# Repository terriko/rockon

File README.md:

# RockOn

Design notes, files and art for a decibel meter soldering kit.

[pyCascades talk slides](
https://docs.google.com/presentation/d/17Rc5WAVUFAWdcNbpMiWgjAE9aOheM9cQXB0_n5h_dbc/edit?usp=sharing)

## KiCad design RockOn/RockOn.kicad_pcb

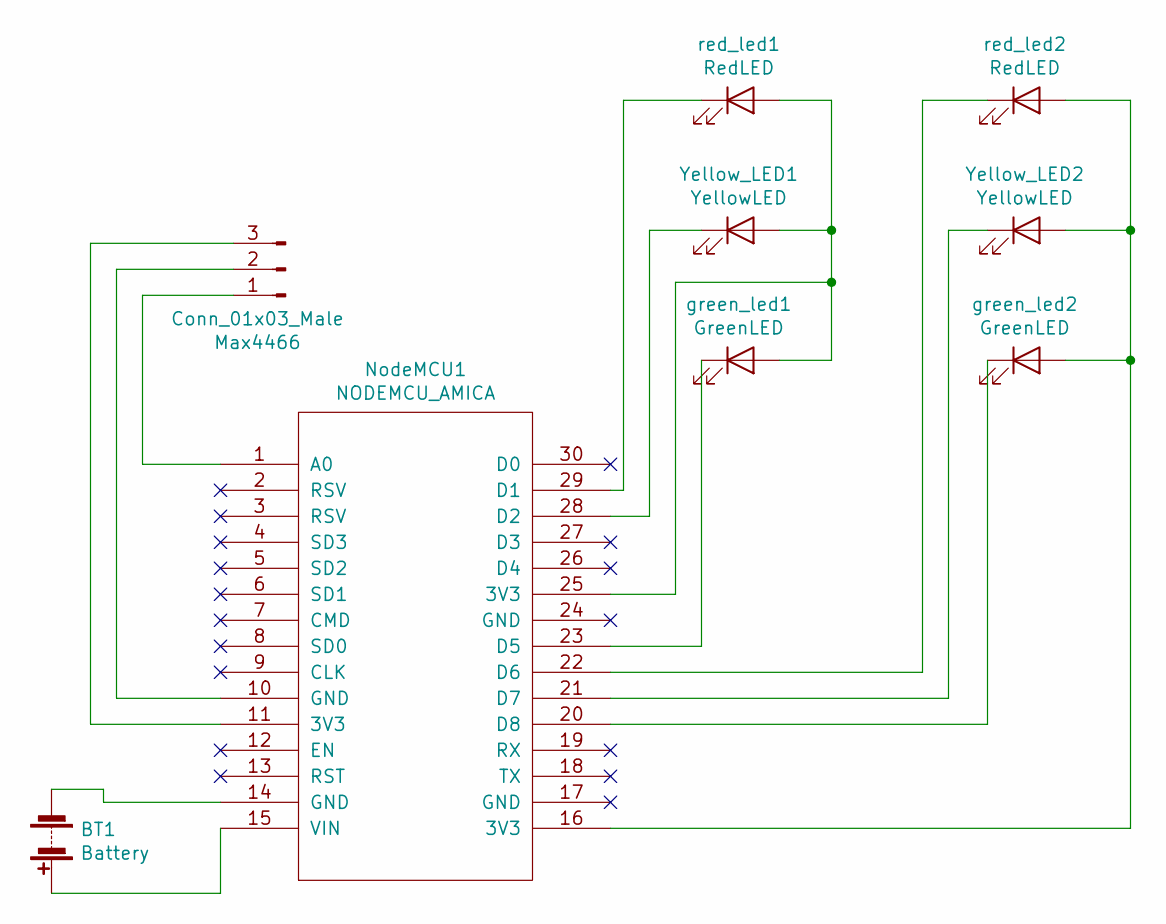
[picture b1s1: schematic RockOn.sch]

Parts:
BT1: Battery; Keystone_2479_3xAAA
Max4466: Conn_01x03_Male; PINHEAD1-3
NodeMCU1: NODEMCU_AMICA; NodeMCU-LoLinV3
Yellow_LED1, Yellow_LED2: YellowLED; LED_D5.0mm
green_led1, green_led2: GreenLED; LED_D5.0mm
red_led1, red_led2: RedLED; LED_D5.0mm

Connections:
unnamed: BT1.1 (+), NodeMCU1.15 (VIN)
unnamed: BT1.2 (-), NodeMCU1.14 (GND)
unnamed: Max4466.1, NodeMCU1.1 (A0)
unnamed: Max4466.2, NodeMCU1.10 (GND)
unnamed: Max4466.3, NodeMCU1.11 (3V3)
unnamed: NodeMCU1.16 (3V3), Yellow_LED2.2 (A), green_led2.2 (A), red_led2.2 (A)
unnamed: NodeMCU1.20 (D8), green_led2.1 (K)
unnamed: NodeMCU1.21 (D7), Yellow_LED2.1 (K)
unnamed: NodeMCU1.22 (D6), red_led2.1 (K)
unnamed: NodeMCU1.23 (D5), green_led1.1 (K)
unnamed: NodeMCU1.25 (3V3), Yellow_LED1.2 (A), green_led1.2 (A), red_led1.2 (A)
unnamed: NodeMCU1.28 (D2), Yellow_LED1.1 (K)
unnamed: NodeMCU1.29 (D1), red_led1.1 (K)

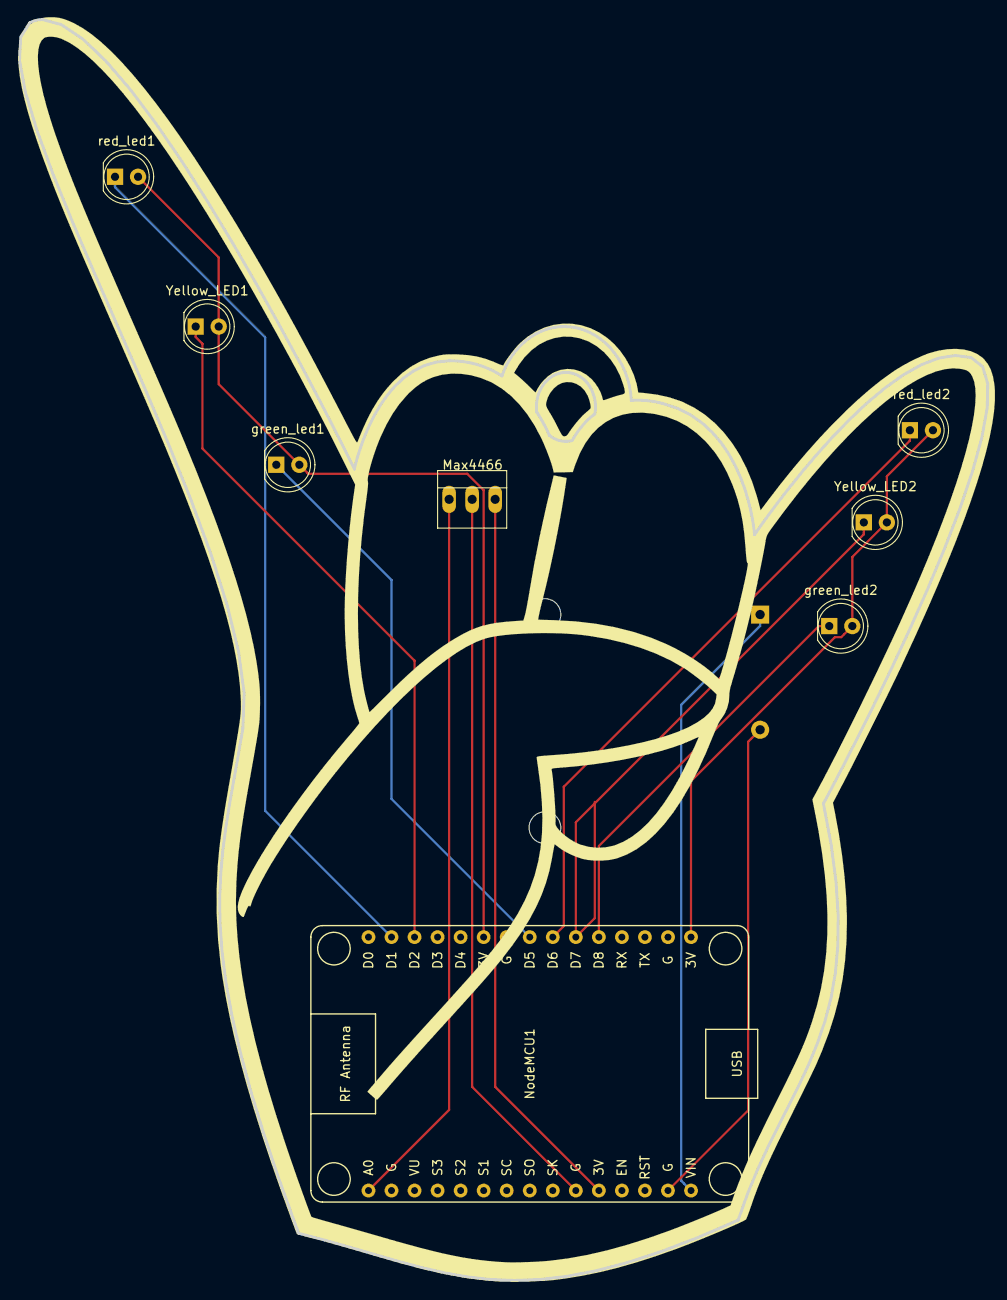
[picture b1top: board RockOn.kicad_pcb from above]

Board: 2 copper layers, 106.7 x 139.0 mm, 10 parts (1 on the bottom side), 13 nets.

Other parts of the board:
Edge1: Edge; RockOn-silkscreen-110mm

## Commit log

2020-01-21 Initial art sketch
2020-02-02 Initial layout start
2020-02-03 Corrected components, silkscreen
2020-02-03 larger silkscreen
2020-02-04 Add mic code
2020-02-04 working simple code, no scaling
2020-02-08 Partially routed
2020-02-08 Quick and lazy routing; needs refinement
2020-02-09 Add presentation link
